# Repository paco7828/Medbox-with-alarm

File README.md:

# Timed Box

Battery-powered time-locked box driven by an ESP32-C3 Supermini. It functions as an interactive alarm clock that uses a servo motor to automatically open at a specific time. It utilizes deep sleep mode to preserve battery life when not actively in use.

## Features

- **Time-Triggered Lockbox:** Automatically triggers a servo to open the box when the programmed alarm goes off. The box automatically closes after 30 seconds.
- **Ultra-Low Power Mode:** Enters deep sleep after 60 seconds of inactivity. Automatically wakes up exactly when the alarm is due or via a manual button press.
- **1.8" TFT Display:** Shows real-time clock, date, day of the week, and current alarm status with optimized rendering.
- **Precision Timekeeping:** Uses a DS3231M RTC circuit to maintain accurate time independently of the MCU.
- **Audio Feedback:** Integrated buzzer plays alarm sequences and button interaction sounds.
- **Manual Override:** Long-pressing the main button allows you to manually open or close the box at any time without an alarm.
- **On-Device Configuration:** Two physical buttons to toggle the alarm state, configure the alarm time, and wake the device from sleep. Alarm times are saved in non-volatile memory.
- **Integrated Power Management:** Runs on a 3.7V LiPo battery. Includes a built-in USB-C charging circuit with battery protection and a boost converter for 5V components.

## Hardware Components

- **MCU:** ESP32-C3 SUPERMINI
- **RTC:** DS3231M
- **Display:** 1.8" TFT Screen (ST7735)
- **Actuator:** Servo Motor
- **Audio:** Active Buzzer
- **Power System:** 3.7V LiPo Battery, TP4056 Battery Charger / Protection module (with 8205A & DW01A), MT3608 Step-up Converter (3.7V -> 5V)
- **Inputs:** 2x Tactile Push Buttons, Power Switch

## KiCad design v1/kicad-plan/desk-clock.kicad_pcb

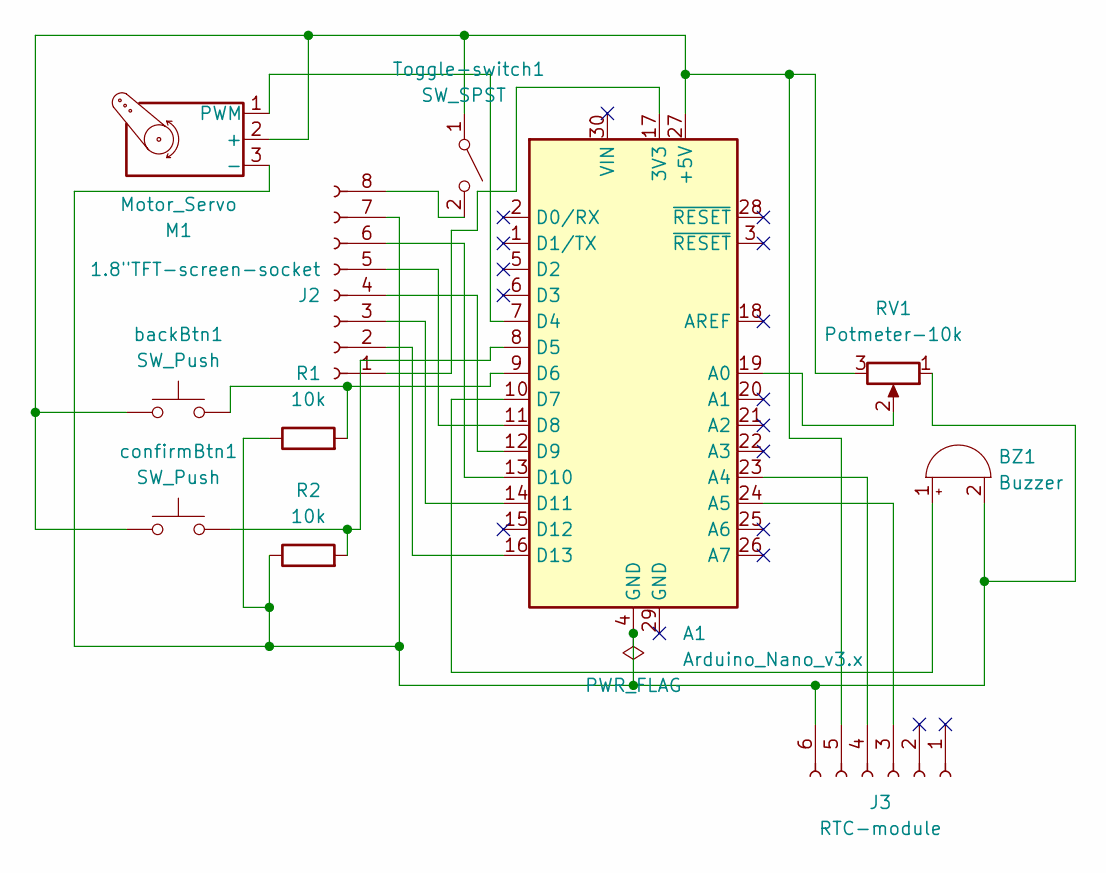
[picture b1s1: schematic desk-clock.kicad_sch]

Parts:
A1: Arduino_Nano_v3.x; Arduino_Nano
BZ1: Buzzer; Buzzer_TDK_PS1240P02BT_D12.2mm_H6.5mm
J2: 1.8"TFT-screen-socket; PinSocket_1x08_P2.54mm_Vertical
J3: RTC-module; PinSocket_1x06_P2.54mm_Vertical
M1: Motor_Servo; PinHeader_1x03_P2.54mm_Vertical
R1, R2: 10k; R_Axial_DIN0207_L6.3mm_D2.5mm_P10.16mm_Horizontal
RV1: Potmeter-10k; Potentiometer_Piher_PC-16_Single_Vertical
Toggle-switch1: SW_SPST; PinSocket_1x03_P2.54mm_Vertical
backBtn1: SW_Push; SW_Push_2P1T_Toggle_CK_PVA1xxH1xxxxxxV2
confirmBtn1: SW_Push; SW_Push_2P1T_Toggle_CK_PVA1xxH1xxxxxxV2

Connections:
unnamed: A1.17 (3V3), J2.1
unnamed: A1.27 (+5V), J3.5, M1.2 (+), RV1.3, Toggle-switch1.1 (A), backBtn1.1, confirmBtn1.1
unnamed: A1.19 (A0), RV1.2
unnamed: A1.23 (A4), J3.4
unnamed: A1.24 (A5), J3.3
unnamed: A1.7 (D4), M1.1 (PWM)
unnamed: A1.8 (D5), R2.2, confirmBtn1.2
unnamed: A1.9 (D6), R1.2, backBtn1.2
unnamed: A1.10 (D7), BZ1.1 (+)
unnamed: A1.11 (D8), J2.5
unnamed: A1.12 (D9), J2.4
unnamed: A1.13 (D10), J2.6
unnamed: A1.14 (D11), J2.3
unnamed: A1.16 (D13), J2.2
unnamed: A1.4 (GND), BZ1.2 (-), J2.7, J3.6, M1.3 (-), R1.1, R2.1, RV1.1
unnamed: J2.8, Toggle-switch1.2 (B)

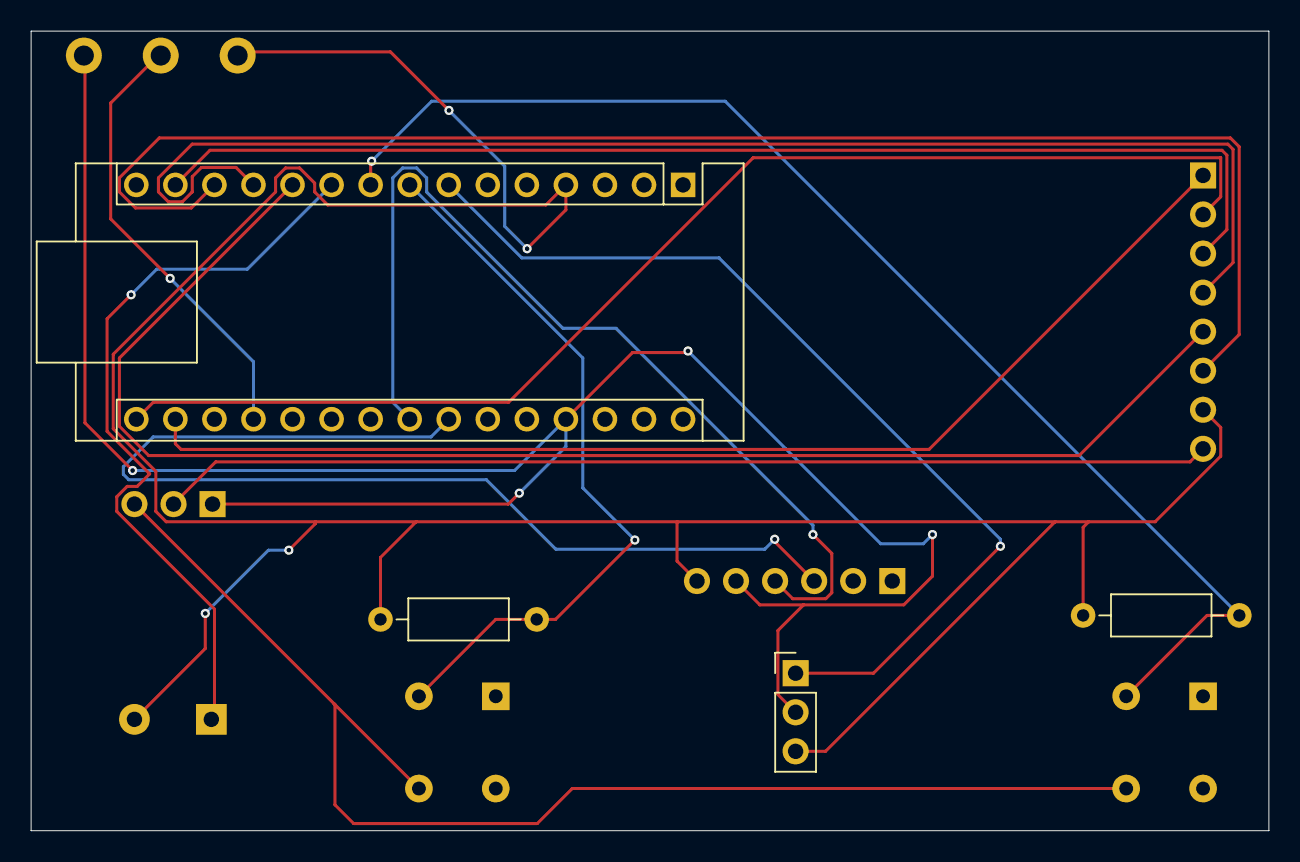
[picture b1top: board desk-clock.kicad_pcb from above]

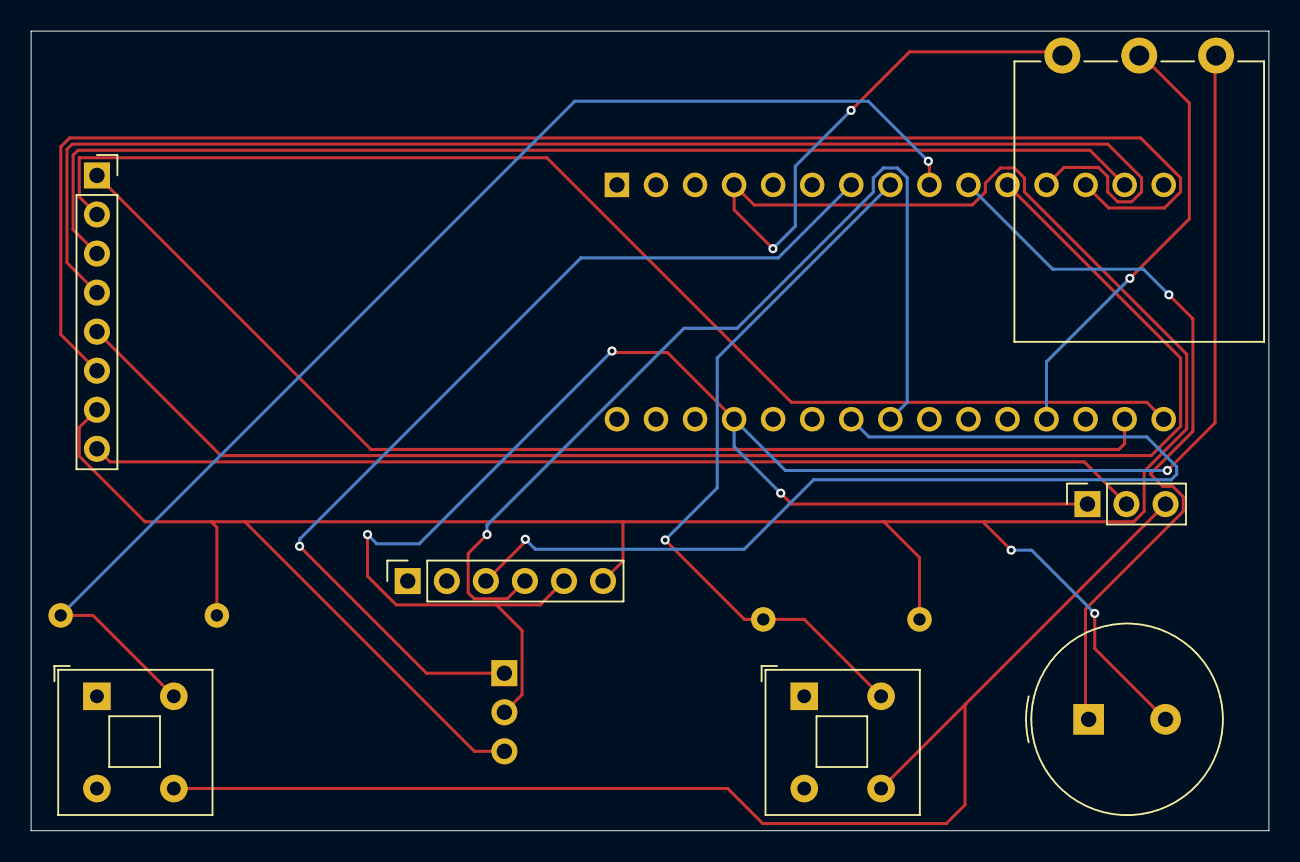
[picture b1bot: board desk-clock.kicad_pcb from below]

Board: 2 copper layers, 80.5 x 52.0 mm, 11 parts (7 on the bottom side), 16 nets.

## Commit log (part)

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2024-10-19 Added description v1
2024-10-19 Added component list v1
2024-10-19 Update Description.txt with seconds
2024-10-19 Added screen's output/display plan layout.
2024-10-19 Added ideas
2024-10-19 Added demo code
2024-10-20 Update desk-clock.ino to display time every seconds
2024-10-20 Update desk-clock.ino - Main screen layout print
2024-10-20 Update desk-clock.ino with confirm + backBtn + alarm (piezo)
2024-10-20 Update desk-clock.ino with setting alarm function (not finished)
2024-10-21 Update desk-clock.ino - backup save before final code
2024-10-21 Update desk-clock.ino - backup save
2024-10-21 Update desk-clock.ino - final code
2024-10-22 Added wiring's visual representation
2024-10-28 Added new wiring plan with servo
2024-10-29 Added 3D representation of the final form.
2024-10-29 Update components.txt with screen's on/off switch
2024-10-29 Added new wiring - extended with screen's switch
2024-10-29 Added visual representation with their correct format
2024-10-29 Update components.txt with a new toggle switch
2024-11-03 Added RTC module's wiring
2024-11-07 Added new kicad plan
2024-11-18 Added models folder to store prototypes and real life models
2024-12-07 Sorted the files, start of compact, smaller build begins.
2024-12-07 To be continued.
2024-12-31 Update med-box-w-alarm.ino with new alarm type
2024-12-31 Changed number of repetitions and volume of alarm.
2024-12-31 Modified code so alarm doesn't interrupt time display + new alarm
2025-12-22 Added V2 code.
2025-12-23 Created new layout for the screen.
2025-12-23 Added new alarm sounding.
2025-12-23 Added deep sleep functionality for power saving feature.
2025-12-26 Added V2 components list.
2025-12-26 Added V2 PCB.
2025-12-27 Changed battery connector polarity on V2 PCB.
2026-01-01 Fixed switched up TFT connections on V2 PCB.
2026-01-03 Added correct medbox v2 pcb.
2026-01-03 Moved V2 PCB to the V2 folder.
2026-01-21 Fixed code with correctly centered time displaying.
2026-01-27 Rotated the display inside code.
2026-02-02 Fixed code opening from deep sleep.
2026-02-11 Removed automated timer.
2026-02-22 Removed servo test sequence from startup.
2026-03-03 Updated code so it calculates wakeup time better and uses less battery.
2026-03-13 Added box-opening logic with button holding.
